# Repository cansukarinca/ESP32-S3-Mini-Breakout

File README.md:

# ESP32-S3 Mini Breakout Board

ESP32-S3-MINI-1 modülü için tasarlanmış, kompakt ve yüksek performanslı bir geliştirme kartı.

## Proje Önizlemesi

## Teknik Özellikler
* **Mikrodenetleyici:** ESP32-S3-MINI-1 (Dahili antenli modül)
* **Güç Girişi:** 5V (Micro-USB / VBUS üzerinden)
* **Voltaj Regülatörü:** TLV75801PDRV (5V -> 3.3V LDO)
* **Koruma:** USB veri hatları için D3V3XA4B10LP ESD koruma diyot dizisi
* **Kontrol:** Fiziksel Reset ve Boot butonları

## Tasarım Detayları
* **Anten Performansı:** RF sinyal kalitesini korumak amacıyla antenin altında tüm katmanlarda bakır girilmez bölge (Keepout Area) tanımlanmıştır.
* **USB Diferansiyel Çifti:** USB veri yolları sinyal bütünlüğü için paralel ve dengeli bir şekilde kurgulanmıştır.
* **PCB Katmanları:** Çift katmanlı (FR4) tasarım.

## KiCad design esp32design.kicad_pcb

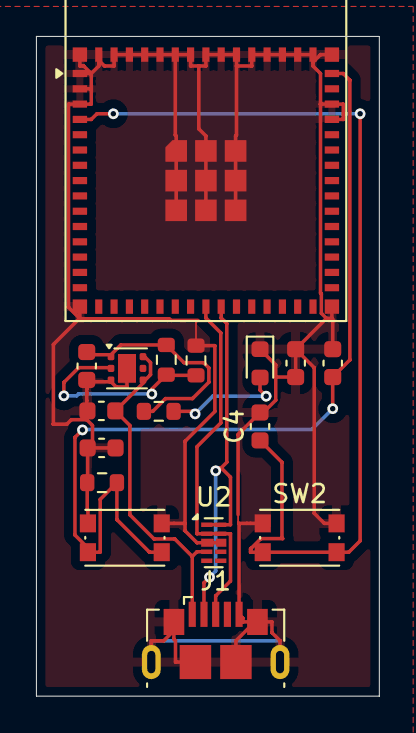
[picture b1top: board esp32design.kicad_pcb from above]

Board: 2 copper layers, 19.0 x 36.7 mm, 17 parts (0 on the bottom side), 9 nets.

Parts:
C1, C3, C4: 0.1uF; C_0603_1608Metric
C2, C5, C6: 10uF; C_0603_1608Metric
D1: LED; LED_0603_1608Metric
J1: USB_B_Micro; USB_Micro-B_GCT_USB3076-30-A
R1: 10K; R_0603_1608Metric
R2: 1M; R_0603_1608Metric
R3: 200K; R_0603_1608Metric
R4: 5.1K; R_0603_1608Metric
SW1: RESET; SW_Push_1P1T_NO_CK_KMR2
SW2: BOOT; SW_Push_1P1T_NO_CK_KMR2
U1: ESP32-S3-MINI-1; ESP32-S2-MINI-1
U2: D3V3XA4B10LP; Diodes_UDFN-10_1.0x2.5mm_P0.5mm
U3: TLV75801PDRV; WSON-6-1EP_2x2mm_P0.65mm_EP1x1.6mm

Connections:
/5VUSB: C6.1, J1.1 (VBUS), U2.4, U3.4 (EN), U3.6 (IN)
/ESP32_EN: C3.1, R1.2, SW1.3 (K), SW1.4 (A), U1.45 (EN)
/GPIO0: C4.1, SW2.3 (K), SW2.4 (A), U1.4 (IO0)
GND: C1.1, C1.2, C2.1, C2.2, C3.2, C4.2, C5.2, C6.2, D1.1 (K), J1.5 (GND), J1.6 (Shield), R1.1, R3.2, SW1.1, SW2.1, U1.1 (GND), U1.2 (GND), U1.3 (3V3), U1.42 (GND), U1.43 (GND), U1.46 (GND), U1.47 (GND), U1.48 (GND), U1.49 (GND), U1.50 (GND), U1.51 (GND), U1.52 (GND), U1.53 (GND), U1.54 (GND), U1.55 (GND), U1.56 (GND), U1.57 (GND), U1.58 (GND), U1.59 (GND), U1.60 (GND), U1.61 (GND), U1.62 (GND), U1.63 (GND), U1.64 (GND), U1.65 (GND), U2.3 (VSS), U2.8 (VSS), U3.3 (GND), U3.7 (GND)
unnamed: D1.2 (A), R4.2
unnamed: R2.2, R3.1, U3.2 (FB)
unnamed: C5.1, R2.1, R4.1, U3.1 (OUT)
USB_N: J1.3 (D+), U1.23 (USB_D-), U2.2, U2.9 (NC)
USB_P: J1.2 (D-), U1.24 (USB_D+), U2.1, U2.10 (NC)

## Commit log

2026-03-03 Rename pcb_3d_view.png.png to pcb_3d_view.png
2026-03-03 Update README with project details and specifications
    Added detailed project overview, technical specifications, and design details for the ESP32-S3 Mini Breakout Board.
